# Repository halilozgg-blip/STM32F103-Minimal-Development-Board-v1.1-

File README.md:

# STM32F103 Minimal Development Board (v1.1)
.png)

##  Project Overview
This project is a custom-designed **STM32F103C8T6** development board created using **KiCad 9.0**. It provides a compact and reliable hardware platform for embedded software development, rapid prototyping, and educational projects.

The design focuses on clean power distribution, hardware protection, modular architecture, and debugging convenience while following recommended PCB design practices.

##  Design Goals
* **Reliable Hardware:** Design a stable and reusable STM32 development platform.
* **Easy Development:** Provide essential interfaces required for firmware development and debugging.
* **Good PCB Practices:** Follow clean schematic organization and PCB layout guidelines.
* **Open Source:** Make the project easy to understand, reproduce, and modify.

##  Key Features

###  Power & Protection
* **USB Type-C** Power Input.
* **USBLC6-2SC6** TVS diode for ESD protection on USB data lines.
* **500 mA** Resettable PTC Polyfuse for overcurrent protection.
* **AMS1117-3.3V** linear regulator providing a stable 3.3V supply.
* Decoupling capacitors placed according to STM32 hardware design recommendations.

###  Microcontroller Hardware
* **STM32F103C8T6** ARM Cortex-M3 microcontroller.
* External crystal oscillator.
* Hardware reset circuit.
* Pull-down resistor on `BOOT0` for reliable boot configuration.
* **SWD** programming and debugging interface.
* Clearly labeled test points for debugging and measurements.

###  Development Features
* User LED.
* User push button.
* GPIO expansion headers.
* Modular schematic hierarchy for easier maintenance and future expansion.

## 📂 Repository Structure
  ```text
STM32F103_Minimal_Development_Board_v1.1
│
├── HARDWARE/        # KiCad Project, Schematics, and PCB Layout
├── PRODUCTION/     # Gerber Files, Drill Files, and Manufacturing Outputs
└── STM32F103 IMAGES AND DOCS/
    ├── Schematic PDF, PCB Images
    ├── 3D Renders
    └── Project Documentation
  ```
#  Hardware Summary

| Component | Description |
| :--- | :--- |
| **MCU** | STM32F103C8T6 |
| **Core** | ARM Cortex-M3 |
| **Operating Voltage** | 3.3 V |
| **Power Input** | USB Type-C |
| **Debug Interface** | SWD |
| **PCB Design** | KiCad 9.0 |

##  Future Improvements
* USB communication support.
* Additional protection circuitry.
* Boot mode selection jumper.
* CAN interface.
* External SPI Flash & I²C EEPROM.
* Additional status indicators.

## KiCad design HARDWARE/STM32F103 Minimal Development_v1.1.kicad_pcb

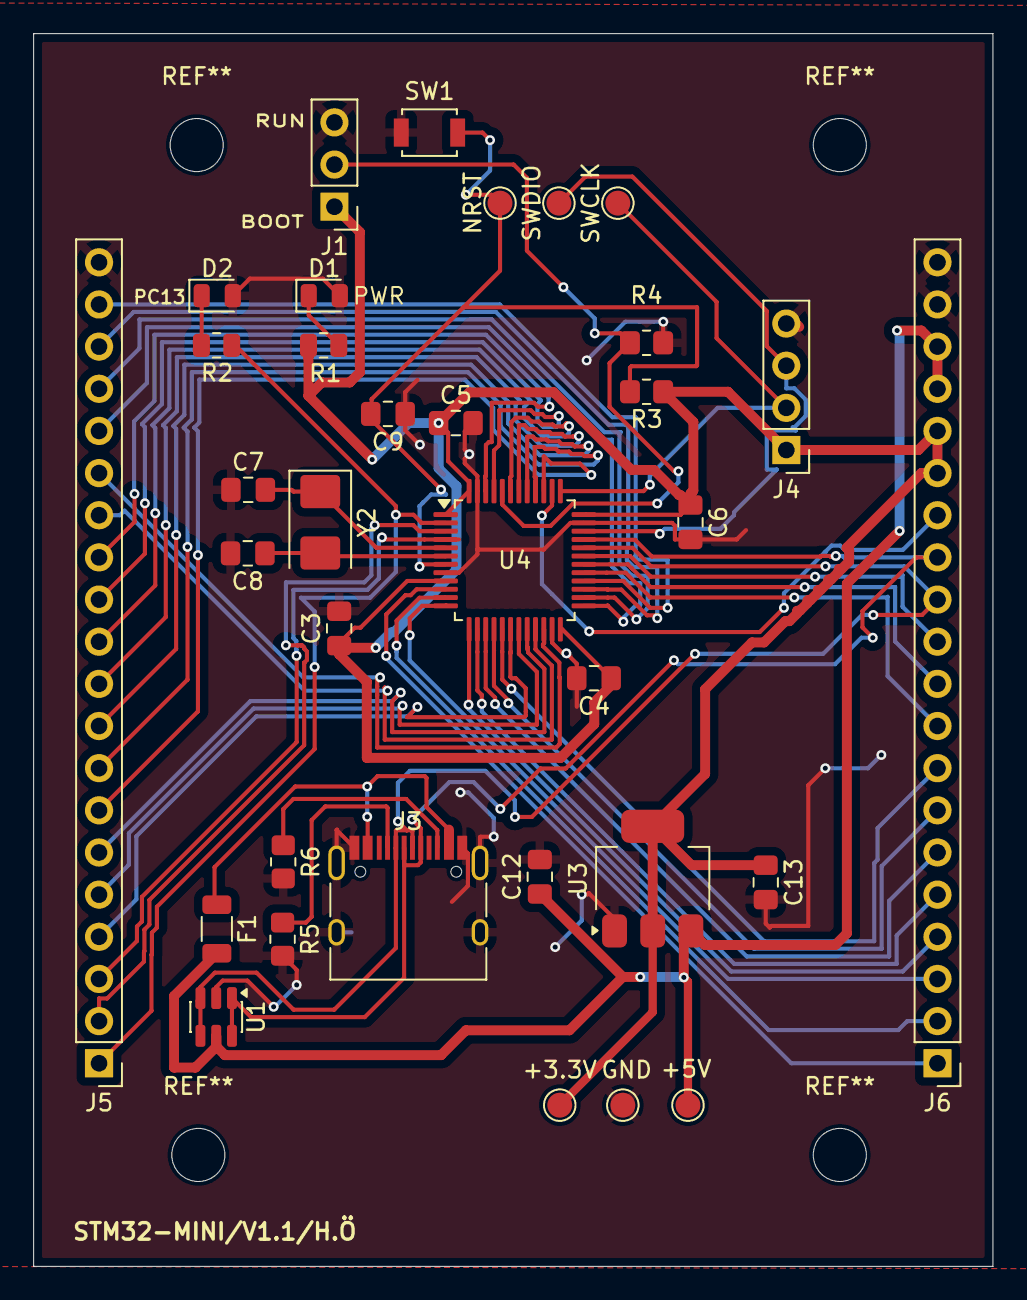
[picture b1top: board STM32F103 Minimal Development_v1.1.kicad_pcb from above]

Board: 2 copper layers, 57.8 x 74.3 mm, 34 parts (0 on the bottom side), 47 nets.

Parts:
+3.3V, +5V: TestPoint; TestPoint_Pad_D1.5mm
C3, C4, C5, C6, C9: 0.1uF; C_0805_2012Metric_Pad1.18x1.45mm_HandSolder
C7, C8: 22pF; C_0805_2012Metric_Pad1.18x1.45mm_HandSolder
C12, C13: 10uF; C_0805_2012Metric_Pad1.18x1.45mm_HandSolder
D1, D2: LED; LED_0805_2012Metric
F1: Polyfuse; R_1206_3216Metric
GND: TestPoint; TestPoint_Pad_D1.5mm
J1: Conn_01x03_Pin; PinHeader_1x03_P2.54mm_Vertical
J3: USB_C_Receptacle_USB2.0_14P; USB_C_Receptacle_HRO_TYPE-C-31-M-12
J4: Conn_01x04_Pin; PinHeader_1x04_P2.54mm_Vertical
J5, J6: Conn_01x20_Pin; PinHeader_1x20_P2.54mm_Vertical
NRST: TestPoint; TestPoint_Pad_D1.5mm
R1, R2: 330; R_0805_2012Metric
R3, R4: 10k; R_0805_2012Metric_Pad1.20x1.40mm_HandSolder
R5, R6: 5.1k; R_0805_2012Metric_Pad1.20x1.40mm_HandSolder
SW1: SW_Push; SW_SPST_B3U-1000P
SWCLK: TestPoint; TestPoint_Pad_D1.5mm
SWDIO: TestPoint; TestPoint_Pad_D1.5mm
U1: USBLC6-2SC6; SOT-23-6
U3: AMS1117-3.3; SOT-223-3_TabPin2
U4: STM32F103C8Tx; LQFP-48_7x7mm_P0.5mm
Y2: 8MHz; Crystal_SMD_5032-2Pin_5.0x3.2mm

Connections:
USB D+: J3.A6 (D+), J3.B6 (D+), J6.13, U1.1 (I/O1), U1.6 (I/O1), U4.33 (PA12)
USB D-: J3.A7 (D-), J3.B7 (D-), J6.12, U1.3 (I/O2), U1.4 (I/O2), U4.32 (PA11)
+3.3V: +3.3V.1, C3.1, C4.1, C5.1, C6.1, C13.1, J1.1, J4.1, J6.15, J6.16, R1.1, R3.1, U3.2 (VO), U4.1 (VBAT), U4.9 (VDDA), U4.24 (VDD), U4.36 (VDD), U4.48 (VDD)
+5V: +5V.1, C12.1, F1.2, J6.17, J6.18, U1.5 (VBUS), U3.3 (VI)
GND: C3.2, C4.2, C5.2, C6.2, C7.1, C8.2, C9.1, C12.2, C13.2, D1.2 (A), D2.2 (A), GND.1, J1.3, J3.A1 (GND), J3.A12 (GND), J3.B1 (GND), J3.B12 (GND), J3.S1 (SHIELD), J4.4, J5.20, J6.19, J6.20, R4.1, R5.2, R6.2, SW1.1, U1.2 (GND), U3.1 (GND), U4.8 (VSSA), U4.23 (VSS), U4.35 (VSS), U4.47 (VSS)
MCU_OSC_IN: C7.2, U4.5 (PD0), Y2.1
MCU_OSC_OUT: C8.1, U4.6 (PD1), Y2.2
MCU_SWCLK: J4.2, SWCLK.1, U4.37 (PA14)
MCU_SWDIO: J4.3, SWDIO.1, U4.34 (PA13)
unnamed: D1.1 (K), R1.2
unnamed: D2.1 (K), R2.1
unnamed: F1.1, J3.A4 (VBUS), J3.A9 (VBUS), J3.B4 (VBUS), J3.B9 (VBUS)
unnamed: J1.2, R4.2, U4.44 (BOOT0)
unnamed: J3.A5 (CC1), R5.1
unnamed: J3.B5 (CC2), R6.1
unnamed: C9.2, NRST.1, R3.2, SW1.2, U4.7 (NRST)
PA0: J6.1, U4.10 (PA0)
PA1: J6.2, U4.11 (PA1)
PA2: J6.3, U4.12 (PA2)
PA3: J6.4, U4.13 (PA3)
PA4: J6.5, U4.14 (PA4)
PA5: J6.6, U4.15 (PA5)
PA6: J6.7, U4.16 (PA6)
PA7: J6.8, U4.17 (PA7)
PA8: J6.9, U4.29 (PA8)
PA9: J6.10, U4.30 (PA9)
PA10: J6.11, U4.31 (PA10)
PA15: J6.14, U4.38 (PA15)
PB0: J5.4, U4.18 (PB0)
PB1: J5.5, U4.19 (PB1)
PB2: J5.6, U4.20 (PB2)
PB3: J5.7, U4.39 (PB3)
PB4: J5.8, U4.40 (PB4)
PB5: J5.9, U4.41 (PB5)
PB6: J5.10, U4.42 (PB6)
PB7: J5.11, U4.43 (PB7)
PB8: J5.12, U4.45 (PB8)
PB9: J5.13, U4.46 (PB9)
PB10: J5.14, U4.21 (PB10)
PB11: J5.15, U4.22 (PB11)
PB12: J5.16, U4.25 (PB12)
PB13: J5.17, U4.26 (PB13)
PB14: J5.18, U4.27 (PB14)
PB15: J5.19, U4.28 (PB15)
PC13: J5.1, R2.2, U4.2 (PC13)
PC14: J5.2, U4.3 (PC14)
PC15: J5.3, U4.4 (PC15)
